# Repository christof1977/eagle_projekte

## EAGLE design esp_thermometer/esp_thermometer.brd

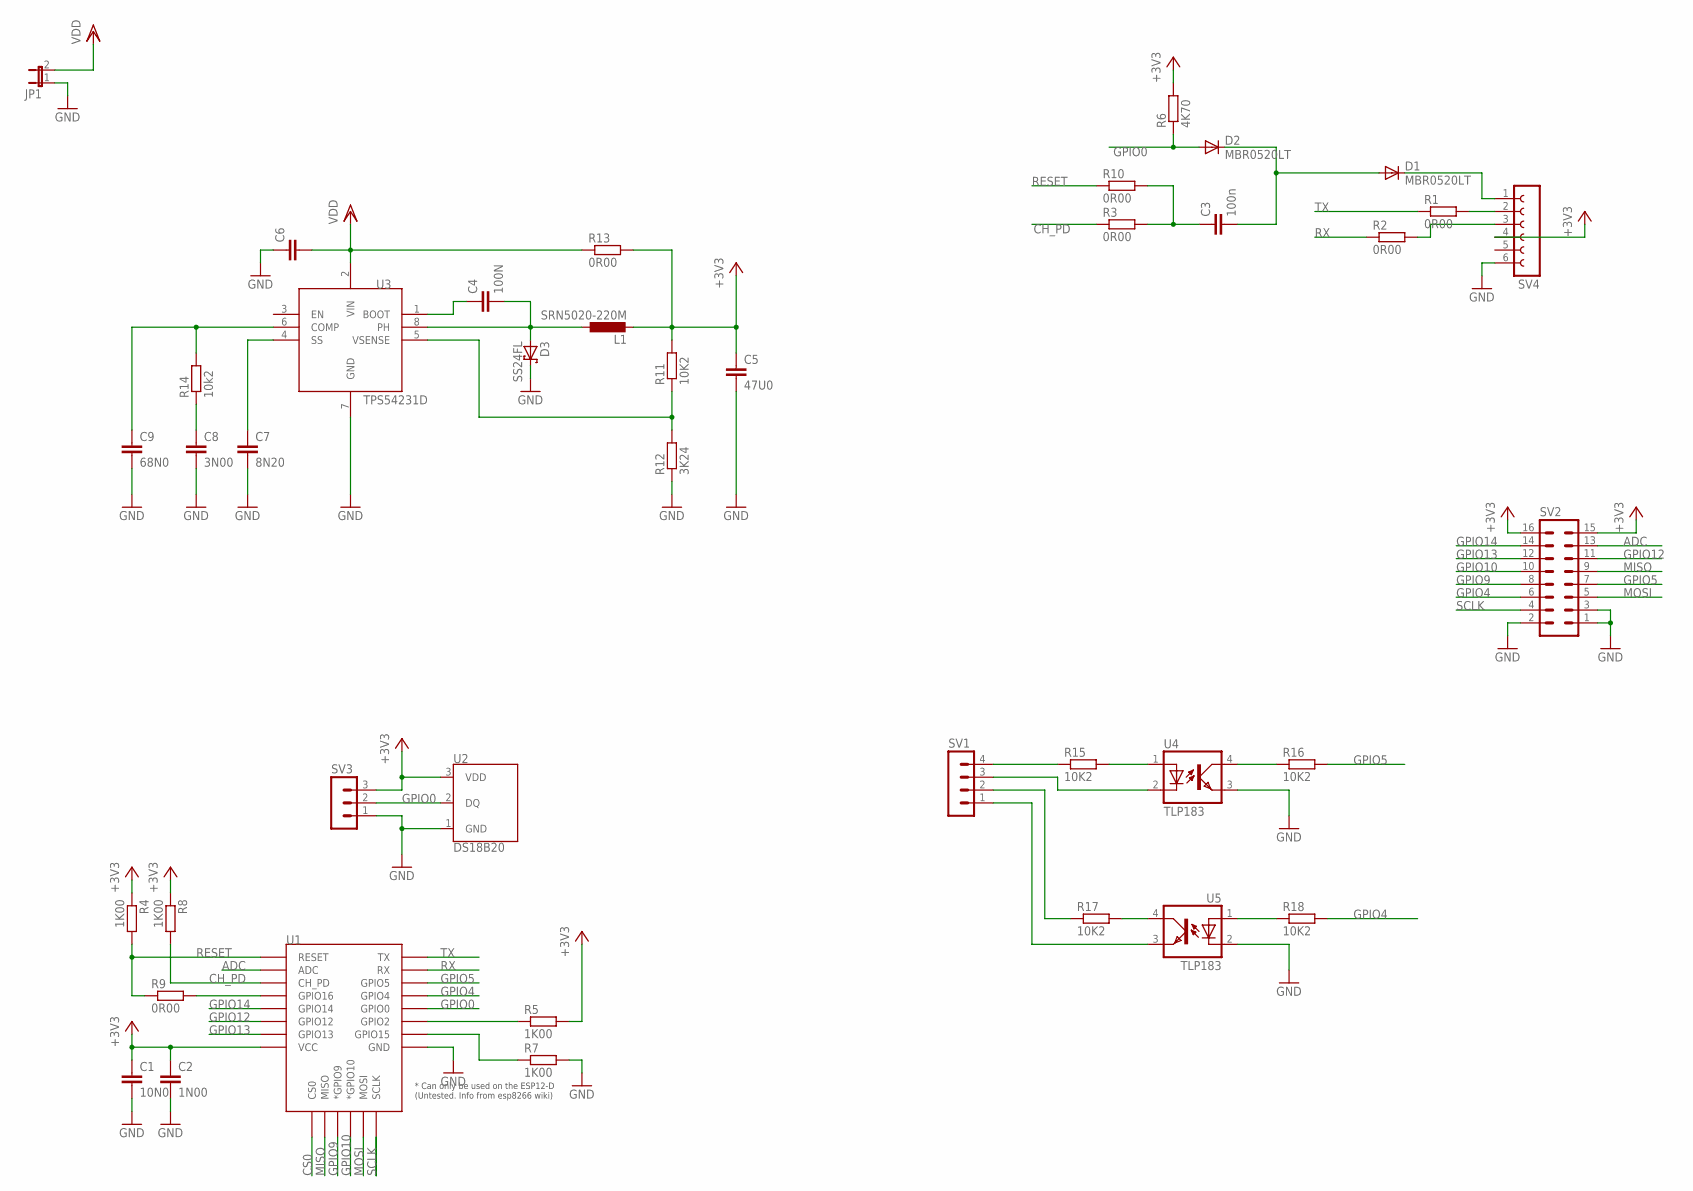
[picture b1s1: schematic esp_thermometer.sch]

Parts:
C1: 10N0; C1206K
C2: 1N00; C1206K
C3: 100n; C1206K
C4: 100N; C0805
C5: 47U0; C1210
C6: C-EUC1210; C1210
C7: 8N20; C0805
C8: 3N00; C0805
C9: 68N0; C0805
D1, D2: MBR0520LT; SOD123
D3: SS24FL; SOD-123_MINI-SMA
JP1: JP1E; JP1
L1: SRN5020-220M; L5050
R1, R2, R3, R9, R10, R13: 0R00; R0805
R4, R5, R7, R8: 1K00; R0805
R6: 4K70; R0805
R11, R15, R16, R17, R18: 10K2; R0805
R12: 3K24; R0805
R14: 10k2; R0805
SV1: MA04-1
SV2: MA08-2
SV3: MA03-1
SV4: FE06-1; FE06
U1: ESP12ESMD; ESP12E-SMD
U2: DS18B20; TO-92-AMMO
U3: TPS54231D; D0008A
U4, U5: TLP183; MINI-FLAT-4

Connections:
+3V3: C1.1, C2.1, C5.1, L1.2, R4.1, R5.2, R6.2, R8.1, R11.2, R13.2, SV2.15, SV2.16, SV3.3, SV4.4, U1.VCC, U2.3 (VDD)
ADC: SV2.13, U1.ADC
CH_PD: R3.1, R8.2, U1.CH_PD
CS0: U1.CS0
GND: C1.2, C2.2, C5.2, C6.1, C7.2, C8.2, C9.2, D3.C, JP1.1, R7.2, R12.1, SV2.1, SV2.2, SV2.3, SV3.1, SV4.6, U1.GND, U2.1 (GND), U3.7 (GND), U4.3 (EMIT), U5.2 (C)
GPIO0: D2.A, R6.1, SV3.2, U1.GPIO0, U2.2 (DQ)
GPIO4: R18.2, SV2.6, U1.GPIO4
GPIO5: R16.2, SV2.7, U1.GPIO5
GPIO9: SV2.8, U1.GPIO9 (*GPIO9)
GPIO10: SV2.10, U1.GPIO10 (*GPIO10)
GPIO12: SV2.11, U1.GPIO12
GPIO13: SV2.12, U1.GPIO13
GPIO14: SV2.14, U1.GPIO14
MISO: SV2.9, U1.MISO
MOSI: SV2.5, U1.MOSI
unnamed: R9.2, U1.GPIO16
unnamed: C4.1, U3.1 (BOOT)
unnamed: R5.1, U1.GPIO2
unnamed: R1.2, SV4.2
unnamed: R7.1, U1.GPIO15
unnamed: R15.2, U4.1 (A)
unnamed: R2.2, SV4.3
unnamed: D1.C, SV4.1
unnamed: C3.2, D1.A, D2.C
unnamed: C3.1, R3.2, R10.2
unnamed: R15.1, SV1.4
unnamed: SV1.3, U4.2 (C)
unnamed: R11.1, R12.2, U3.5 (VSENSE)
unnamed: R17.1, SV1.2
unnamed: C7.1, U3.4 (SS)
unnamed: C8.1, R14.1
unnamed: C9.1, R14.2, U3.6 (COMP)
unnamed: R17.2, U5.4 (COL)
unnamed: R16.1, U4.4 (COL)
unnamed: SV1.1, U5.3 (EMIT)
unnamed: R18.1, U5.1 (A)
PH: C4.2, D3.A, L1.1, U3.8 (PH)
RESET: R4.2, R9.1, R10.1, U1.RESET
RX: R2.1, U1.RXD0 (RX)
SCLK: SV2.4, U1.SCLK
TX: R1.1, U1.TXD0 (TX)
VDD: C6.2, JP1.2, R13.1, U3.2 (VIN)

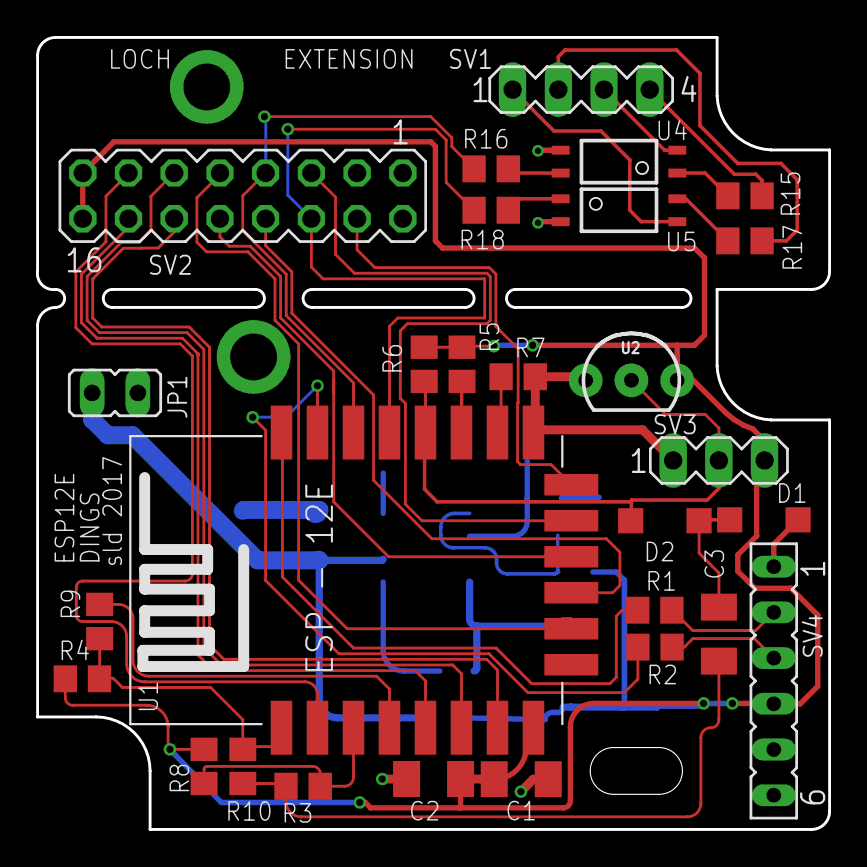
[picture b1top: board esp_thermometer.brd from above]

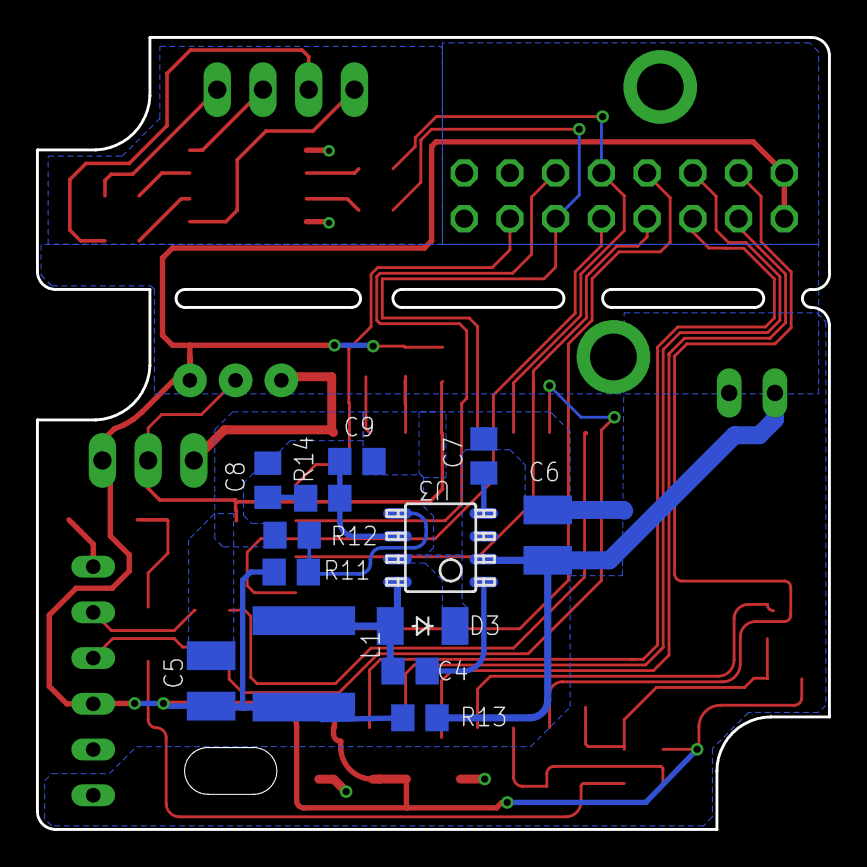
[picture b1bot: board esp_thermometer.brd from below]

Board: 2 copper layers, 44.0 x 44.0 mm, 41 parts (13 on the bottom side), 41 nets.

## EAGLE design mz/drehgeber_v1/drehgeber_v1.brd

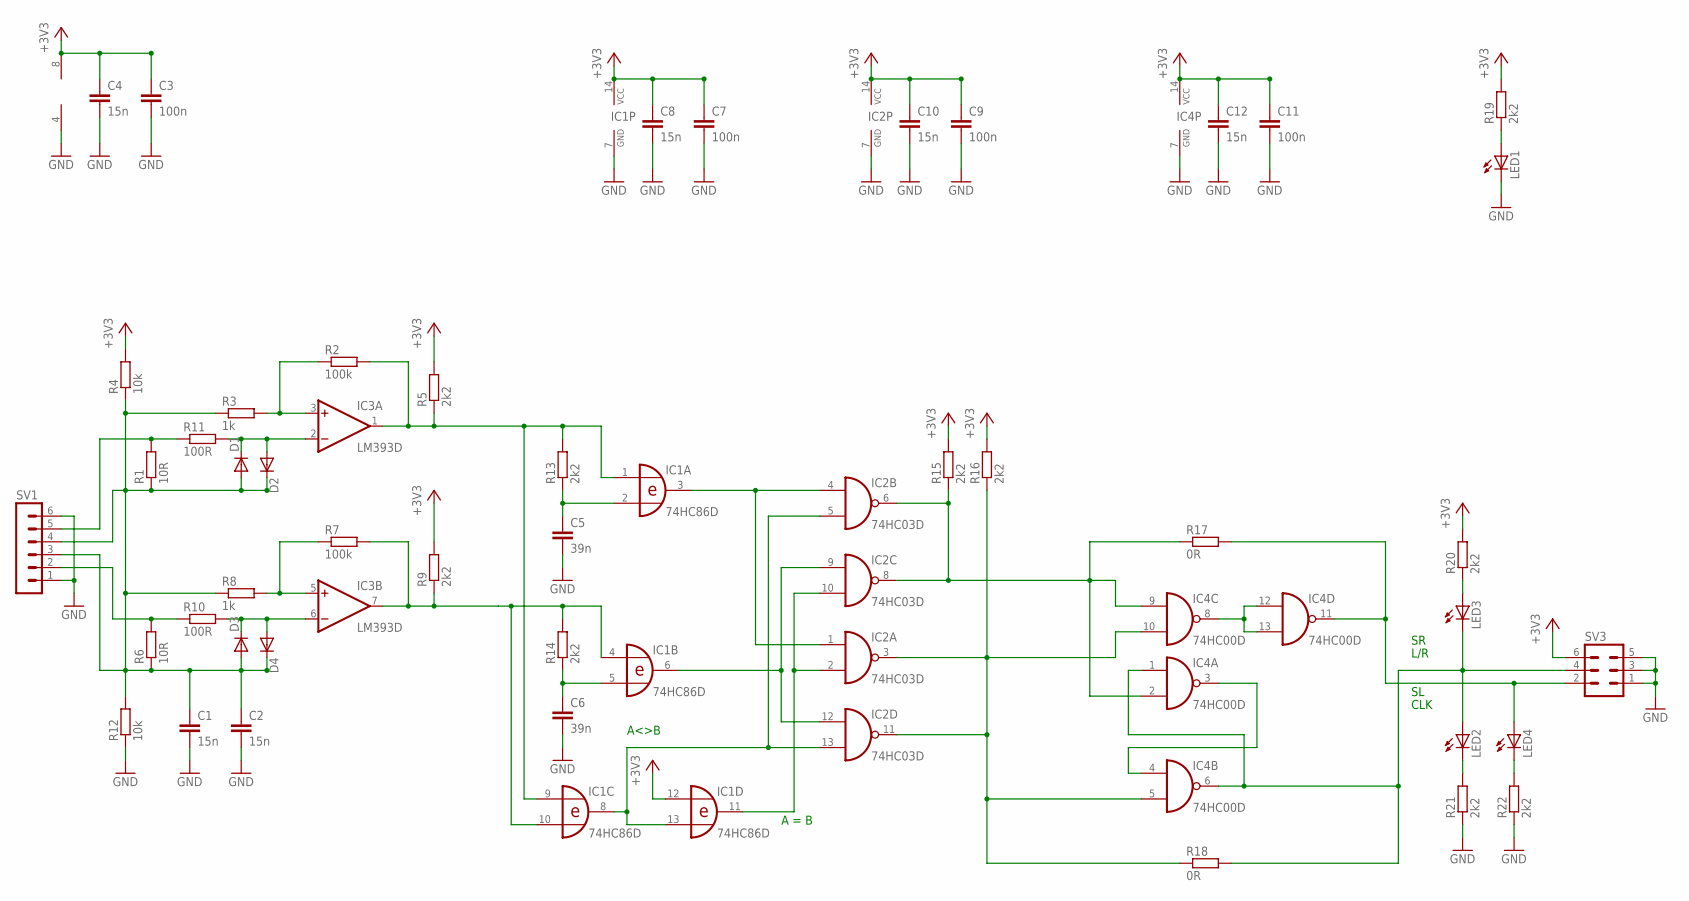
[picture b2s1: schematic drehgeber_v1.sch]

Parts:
C1, C2, C4, C8, C10, C12: 15n; C0805
C3, C7, C9, C11: 100n; C0805
C5, C6: 39n; C0805
D1, D2, D3, D4: DIODE-MINIMELF; MINIMELF
IC1: 74HC86D; SO14
IC2: 74HC03D; SO14
IC3: LM393D; SO08
IC4: 74HC00D; SO14
LED1, LED2, LED3, LED4: LEDCHIPLED_0805; CHIPLED_0805
R1, R6: 10R; R0805
R2, R7: 100k; R0805
R3, R8: 1k; R0805
R4, R12: 10k; R0805
R5, R9, R13, R14, R15, R16, R19, R20, R21, R22: 2k2; R0805
R10, R11: 100R; R1206
R17, R18: 0R; R0805
SV1: MA06-1
SV3: MA03-2

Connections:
+3V3: C3.1, C4.1, C7.1, C8.1, C9.1, C10.1, C11.1, C12.1, IC1.12 (I0), IC1.14 (VCC), IC2.14 (VCC), IC3.8 (V+), IC4.14 (VCC), R4.2, R5.2, R9.2, R15.2, R16.2, R19.2, R20.2, SV3.6
GND: C1.2, C2.2, C3.2, C4.2, C5.2, C6.2, C7.2, C8.2, C9.2, C10.2, C11.2, C12.2, IC1.7 (GND), IC2.7 (GND), IC3.4 (V-), IC4.7 (GND), LED1.C, R12.1, R21.1, R22.1, SV1.1, SV1.6, SV3.1, SV3.3, SV3.5
unnamed: R1.2, R11.1, SV1.5
unnamed: C1.1, C2.1, D1.A, D2.C, D3.A, D4.C, R1.1, R3.1, R4.1, R6.1, R8.1, R12.2, SV1.3, SV1.4
unnamed: D3.C, D4.A, IC3.6 (-IN), R10.2
unnamed: IC3.3 (+IN), R2.1, R3.2
unnamed: IC1.1 (I0), IC1.9 (I0), IC3.1 (OUT), R2.2, R5.1, R13.2
unnamed: R6.2, R10.1, SV1.2
unnamed: D1.C, D2.A, IC3.2 (-IN), R11.2
unnamed: IC3.5 (+IN), R7.1, R8.2
unnamed: IC1.4 (I0), IC1.10 (I1), IC3.7 (OUT), R7.2, R9.1, R14.2
unnamed: C5.1, IC1.2 (I1), R13.1
unnamed: C6.1, IC1.5 (I1), R14.1
unnamed: IC4.11 (O), LED4.A, R17.2, SV3.2
unnamed: LED1.A, R19.1
unnamed: LED4.C, R22.2
unnamed: IC1.8 (O), IC1.13 (I1), IC2.5 (I1), IC2.13 (I1)
unnamed: IC1.3 (O), IC2.1 (I0), IC2.4 (I0)
unnamed: LED2.C, R21.2
unnamed: IC1.6 (O), IC2.9 (I0), IC2.12 (I0)
unnamed: LED3.A, R20.1
unnamed: IC1.11 (O), IC2.2 (I1), IC2.10 (I1)
unnamed: IC2.6 (O), IC2.8 (O), IC4.2 (I1), IC4.9 (I0), R15.1, R17.1
unnamed: IC2.3 (O), IC2.11 (O), IC4.5 (I1), IC4.10 (I1), R16.1, R18.1
unnamed: IC4.8 (O), IC4.12 (I0), IC4.13 (I1)
unnamed: IC4.3 (O), IC4.4 (I0)
unnamed: IC4.1 (I0), IC4.6 (O), LED2.A, LED3.C, R18.2, SV3.4

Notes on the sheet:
CLK
L/R
A<>B
A = B

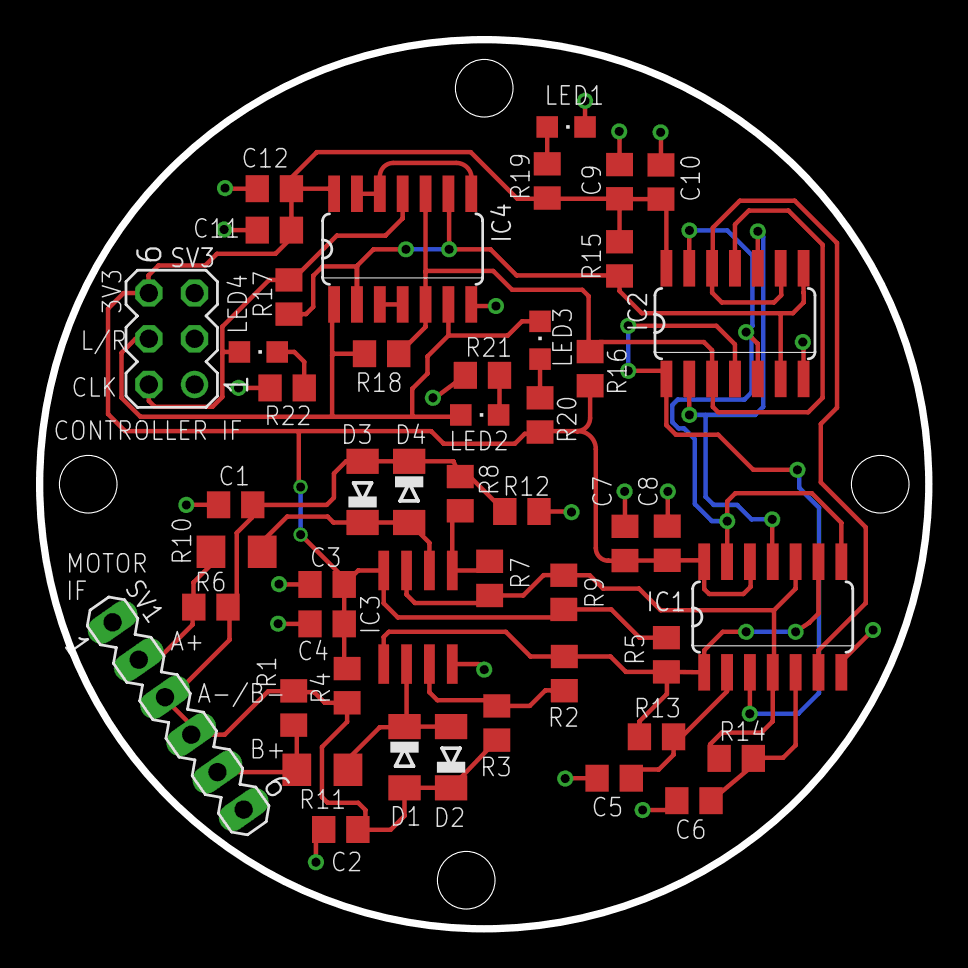
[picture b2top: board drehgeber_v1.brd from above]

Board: 2 copper layers, 49.4 x 49.4 mm, 48 parts (0 on the bottom side), 27 nets.

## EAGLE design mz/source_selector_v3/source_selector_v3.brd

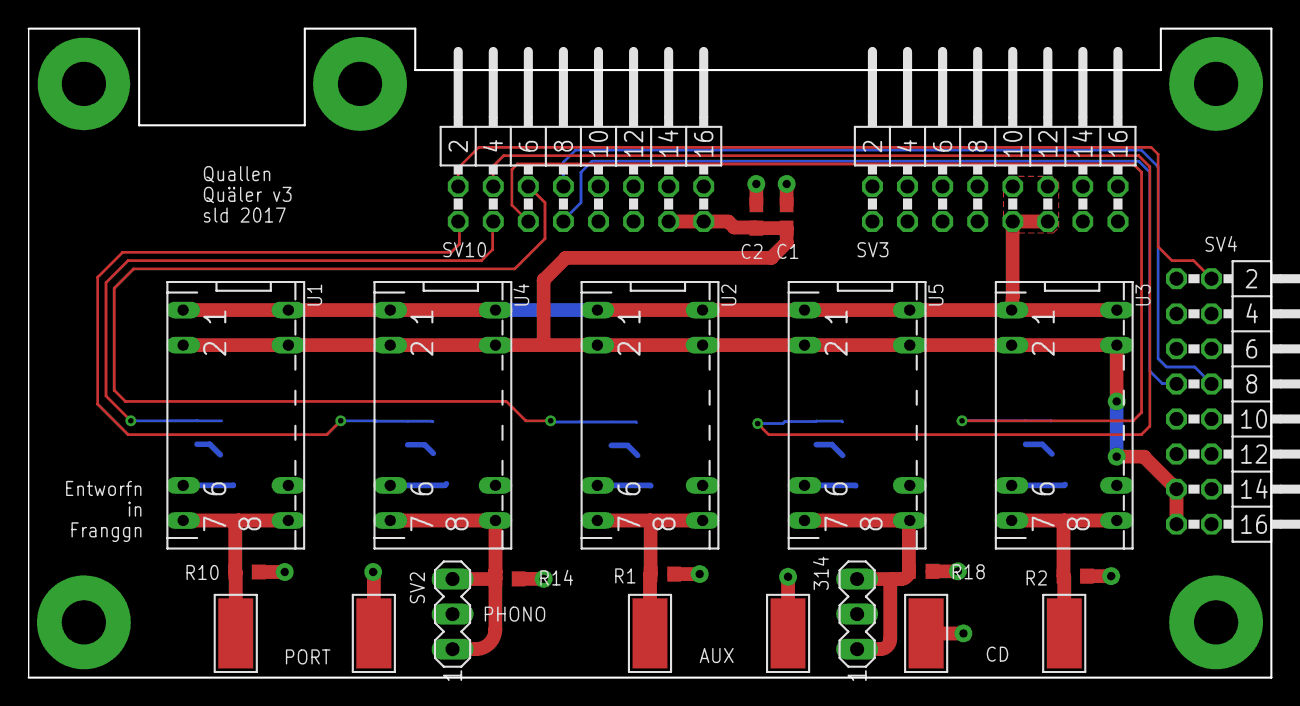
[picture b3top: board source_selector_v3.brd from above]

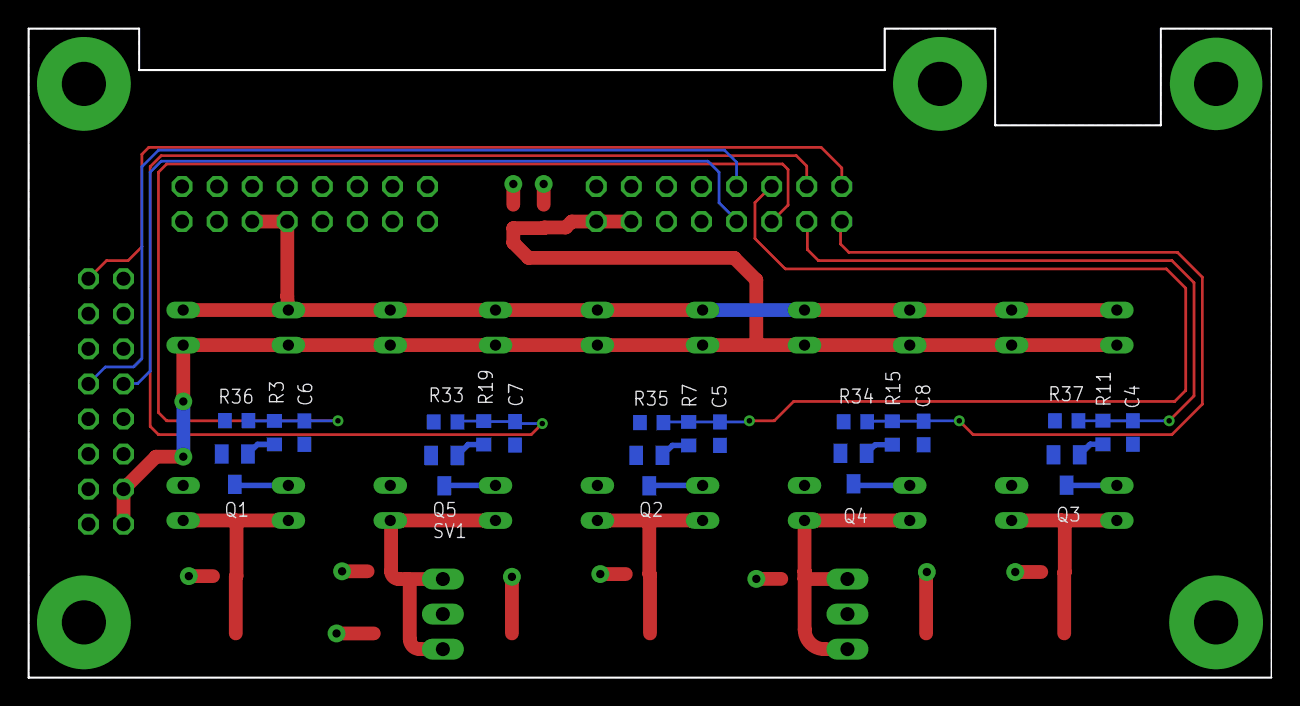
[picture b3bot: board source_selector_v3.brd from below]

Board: 2 copper layers, 90.0 x 47.0 mm, 43 parts (20 on the bottom side), 26 nets.

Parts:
C1: 10n; C0603
C2, C4, C5, C6, C7, C8: 100n; C0603
PAD1, PAD2, PAD3, PAD4, PAD5, PAD6: WIREPADSMD5-2,5; 5-2,5
Q1, Q2, Q3, Q4, Q5: BC847CSMD; SOT23
R1, R2, R10, R14, R18: 1M; R0603
R3, R7, R11, R15, R19: 10k; R0603
R33, R34, R35, R36, R37: 2k2; R0603
SV1, SV2: MA03-1
SV3, SV4, SV10: MA08-2W
U1, U2, U3, U4, U5: DIP7212-D5V; DP-07

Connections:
+5V: C1.1, C2.1, SV4.13, SV4.15, SV10.13, SV10.15, U1.2, U1.13, U2.2, U2.13, U3.2, U3.13, U4.2, U4.13, U5.2, U5.13
AGND: C1.2, C2.2, C4.2, C5.2, C6.2, C7.2, C8.2, PAD2.1, PAD4.1, PAD6.1, Q1.2, Q2.2, Q3.2, Q4.2, Q5.2, R1.1, R2.1, R10.1, R14.1, R18.1, R33.2, R34.2, R35.2, R36.2, R37.2, SV1.2, SV2.2, SV3.1, SV3.2, SV3.3, SV3.4, SV3.5, SV3.6, SV3.7, SV3.8, SV3.13, SV3.14, SV3.15, SV3.16, SV4.9, SV4.10, SV4.11, SV4.14, SV10.9, SV10.10, SV10.11, SV10.14
AMP_OUT: SV4.8, SV10.8
AUX_IN: C5.1, R7.2, R35.1, SV10.6
BYPASS_IN: SV4.2, SV10.2
CD_IN: C6.1, R3.2, R36.1, SV10.5
DAC_IN: C7.1, R19.2, R33.1, SV10.4
HEAD_OUT: SV4.7, SV10.7
unnamed: PAD5.1, R2.2, U3.7, U3.8
unnamed: Q1.1, R3.1
unnamed: Q1.3, U3.6
unnamed: PAD3.1, R1.2, U2.7, U2.8
unnamed: Q2.1, R7.1
unnamed: Q2.3, U2.6
unnamed: PAD1.1, R10.2, U1.7, U1.8
unnamed: Q3.1, R11.1
unnamed: Q3.3, U1.6
unnamed: R14.2, SV2.1, SV2.3, U4.7, U4.8
unnamed: Q4.1, R15.1
unnamed: Q4.3, U4.6
unnamed: R18.2, SV1.1, SV1.3, U5.7, U5.8
unnamed: Q5.1, R19.1
unnamed: Q5.3, U5.6
PHONO_IN: C8.1, R15.2, R34.1, SV10.1
PORTABLE_IN: C4.1, R11.2, R37.1, SV10.3
SUM: SV3.9, SV3.10, SV3.11, SV3.12, U1.1, U1.14, U2.1, U2.14, U3.1, U3.14, U4.1, U4.14, U5.1, U5.14

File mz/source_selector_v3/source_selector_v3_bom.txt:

Stückliste exportiert aus /Volumes/christof's home/eagle/mz/source_selector_v3/source_selector_v3.sch am 21.12.17 21:02

Part Value           Device          Package Description                  MF MPN OC_FARNELL OC_NEWARK
C1   10n             C-EUC0603       C0603   CAPACITOR, European symbol                              
C2   100n            C-EUC0603       C0603   CAPACITOR, European symbol                              
C4   100n            C-EUC0603       C0603   CAPACITOR, European symbol                              
C5   100n            C-EUC0603       C0603   CAPACITOR, European symbol                              
C6   100n            C-EUC0603       C0603   CAPACITOR, European symbol                              
C7   100n            C-EUC0603       C0603   CAPACITOR, European symbol                              
C8   100n            C-EUC0603       C0603   CAPACITOR, European symbol                              
PAD1 WIREPADSMD5-2,5 WIREPADSMD5-2,5 5-2,5   Wire PAD connect wire on PCB                            
PAD2 WIREPADSMD5-2,5 WIREPADSMD5-2,5 5-2,5   Wire PAD connect wire on PCB                            
PAD3 WIREPADSMD5-2,5 WIREPADSMD5-2,5 5-2,5   Wire PAD connect wire on PCB                            
PAD4 WIREPADSMD5-2,5 WIREPADSMD5-2,5 5-2,5   Wire PAD connect wire on PCB                            
PAD5 WIREPADSMD5-2,5 WIREPADSMD5-2,5 5-2,5   Wire PAD connect wire on PCB                            
PAD6 WIREPADSMD5-2,5 WIREPADSMD5-2,5 5-2,5   Wire PAD connect wire on PCB                            
Q1   BC847CSMD       BC847CSMD       SOT23   NPN Transistor                                          
Q2   BC847CSMD       BC847CSMD       SOT23   NPN Transistor                                          
Q3   BC847CSMD       BC847CSMD       SOT23   NPN Transistor                                          
Q4   BC847CSMD       BC847CSMD       SOT23   NPN Transistor                                          
Q5   BC847CSMD       BC847CSMD       SOT23   NPN Transistor                                          
R1   1M              R-EU_R0603      R0603   RESISTOR, European symbol                               
R2   1M              R-EU_R0603      R0603   RESISTOR, European symbol                               
R3   10k             R-EU_R0603      R0603   RESISTOR, European symbol                               
R7   10k             R-EU_R0603      R0603   RESISTOR, European symbol                               
R10  1M              R-EU_R0603      R0603   RESISTOR, European symbol                               
R11  10k             R-EU_R0603      R0603   RESISTOR, European symbol                               
R14  1M              R-EU_R0603      R0603   RESISTOR, European symbol                               
R15  10k             R-EU_R0603      R0603   RESISTOR, European symbol                               
R18  1M              R-EU_R0603      R0603   RESISTOR, European symbol                               
R19  10k             R-EU_R0603      R0603   RESISTOR, European symbol                               
R33  2k2             R-EU_R0603      R0603   RESISTOR, European symbol                               
R34  2k2             R-EU_R0603      R0603   RESISTOR, European symbol                               
R35  2k2             R-EU_R0603      R0603   RESISTOR, European symbol                               
R36  2k2             R-EU_R0603      R0603   RESISTOR, European symbol                               
R37  2k2             R-EU_R0603      R0603   RESISTOR, European symbol                               
SV1                  MA03-1          MA03-1  PIN HEADER                          unknown    unknown  
SV2                  MA03-1          MA03-1  PIN HEADER                          unknown    unknown  
SV3                  MA08-2W         MA08-2W PIN HEADER                          unknown    unknown  
SV4                  MA08-2W         MA08-2W PIN HEADER                          unknown    unknown  
SV10                 MA08-2W         MA08-2W PIN HEADER                          unknown    unknown  
U1   DIP7212-D5V     DIP7212-D5V     DP-07   Meder DIP 7212-D 5V                                     
U2   DIP7212-D5V     DIP7212-D5V     DP-07   Meder DIP 7212-D 5V                                     
U3   DIP7212-D5V     DIP7212-D5V     DP-07   Meder DIP 7212-D 5V                                     
U4   DIP7212-D5V     DIP7212-D5V     DP-07   Meder DIP 7212-D 5V                                     
U5   DIP7212-D5V     DIP7212-D5V     DP-07   Meder DIP 7212-D 5V

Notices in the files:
parts and their libraries:
SparkFun-Sensors: Licensing: Creative Commons ShareAlike 4.0 International - https://creativecommons.org/licenses/by-sa/4.0
